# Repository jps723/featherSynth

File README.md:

# Feather Synth Build Notes 9/4/20

A dual-oscillator polyphonic synthesizer project in collaboration with [Bantam Tools](https://www.bantamtools.com/).  The [project build](https://www.hackster.io/news/create-a-synth-and-sequencer-using-bantam-tools-desktop-cnc-milling-machine-83a0fdb942a3) guide is available on Hackster.

**Design Notes:**

The hardware component of this project is centered around the Adafruit Feather M4 Express.  This board has two 12bit DAC pins allowing for stereo audio synthesis, however this project does not use any stereo effects and delivers a mono signal to a 3.5mm mono audio jack.  

The hardware design has 5 inputs in the form of 4 potentiometers and a tactile button.  There are exposed female headers for an Adafruit Feather M4 Express.  The board will only fit in one direction, with the microUSB port facing to the left.  

If you look at the [pinout](https://learn.adafruit.com/adafruit-feather-m4-express-atsamd51/pinouts) of the M4 Express, you’ll see that we are using analog pin A0 as our DAC/audio output, and A2-A5 as our analog inputs.  Our button connects to digital pin 5.

The base software for the device uses these inputs to control an auto-advancing sequence of notes.  The knobs control the root note, the scale (it comes pre-programmed with the 7 diatonic modes), the probability that the note will play, and the time delay between notes/tempo.  Pressing the button will cycle through different waveforms/oscillator types.

**Synthesizer Design**
The synth is a polyphonic dual-oscillator synthesizer, each with independent bi-quad filters and envelopes.  The envelope settings are static while the filters are set to Low Pass Filters with the frequency cutoff randomly changing between two static values based on probability (math within the software -- this is unrelated to the probability knob).   

**Controls**
Root Note (Tonic)
The note from which the scale begins.  By default the notes to choose from range from A0 to C8

**Scale Selector**
There are a total of seven scales to choose from, beginning with the major scale, and then each mode variant resulting in the 7 diatonic modes in western music.

**Probability**
The probability that the note will be played, as calculated by comparing the knob’s position to a randomly generated number. Ex. 0-100% chance of playing

**Tempo**
The overall tempo of the sequence as determined by delay between each note

**Waveform Selector**
This is a series of oscillator combinations that get cycled through using the button.

## **Code**
The code is broken up into two separate files:  

**featherSynth.ino**
This is our primary code and is broken up into two sections: setup and loop.  Setup runs once, while loop cycles through continuously after the setup code has been executed. All of the code above the setup() function is required to call the library we are using (Audio.h), call our reference file (scales.h), and initialize our global variables. All of the code below the main loop() are functions that are called from either within setup() or loop().

Setup() contains code for setting audio memory allocation, pin assignment, and a function called oscillatorSetup() that is used for setting initial values of our oscillators/envelopes, etc.  These will mostly get overwritten by the loop however we want to define our instrument before the program begins to cycle.  

loop() contains the bulk of our code. We have a function called buttonHandler() that is used for managing what we want to happen when we press the button. If you find this function below, you can add further oscillator combinations.  Our potentiometer readings are assigned to the Feather pins here as well. If you want to change the order of the knobs, do it here.

The nested for() loop is used to populate the rootScaled array.  This determines what notes are in the sequence and the order that they’re arranged in.  There are two arrangements to choose from, either climbing the scale, or random selection.  Only one can be used at a time.

The frequency is calculated using a formula that stems from midi note values which are a standard form of notation for relating to frequency.

The frequency cutoff is currently assigned a 50% chance of being 7000 hz, or 2000 hz.  Experiment with these numbers.

The probabilityOfPlaying variable is compared to a random value between 0 and 100.  Since probabilityOfPlaying is also a value between 0 and 100, this is treated as a percentage.  You can experiment with these values.

playOsc1() and playOsc2() functions take one argument (frequency) which is calculated via the explanation above.  These functions also contain the methods for dictating the ADSR envelope values which are hardcoded and can be adjusted and should be experimented with.  The filter frequency cutoff and delayTime are also embedded in these functions, with delayTime being used to set the time between notes (our tempo).

The buttonHandler function counts the button presses and uses that count to cycle through the 7 different oscillator combinations in the switch statement.

scales.h
scales.h is a reference file where we have all of our different scales stored.  The base code has 7 scales (each of the diatonic modes) spread out across two octaves, with the root note at each octave playing at a 3:1 ratio to everything else.  This results in an 18 note array (an array with 18 indices), which are all a part of another array that contains each of these arrays (a total of 7).  If you were to add an 8th scale with 18 notes, then the scales[][] array should be initialized as scales[8][18].  This would also need to be changed in the .ino sketch in the rootScaled[][] array.  

Currently, if the knob is turned all the way to the left, the Ionian (major) Scale is selected.  As the knob is turned to the right, each scale from the array is played in the order that they are presented in the scales.h file.

## Build Process

**TOP**
Bit: 1/64”
Mill Time: ~3mins

**BOTTOM**
Bit: 1/32”, 1/64”
Mill Time: ~11mins

It’s easiest to solder in this order:
```
1. Vias
2. Resistor
3. Headers
4. Audio jack
5. Tactile button
6. Pots
```

Test

First follow [this guide](https://learn.adafruit.com/adafruit-feather-m4-express-atsamd51) for getting acquainted with the board and setting up your arduino IDE to use it. For the SAMD Board Support (Adafruit version), version 1.5.14 is verified to work.  Version 1.6+ has introduced a problem that will break the code without generating any errors.

Additionally, you will need to install the Adafruit fork of the PJRC Audio Library via the IDE.  

And also the following libraries:

```
Adafruit_SPIFlash
Adafruit_Zero_I2S_Library
SDFat-Adafruit Fork
```

Once all of the dependencies have been installed, and you’ve uploaded a trial sketch, upload the code that you’ve downloaded from the repository and have fun!

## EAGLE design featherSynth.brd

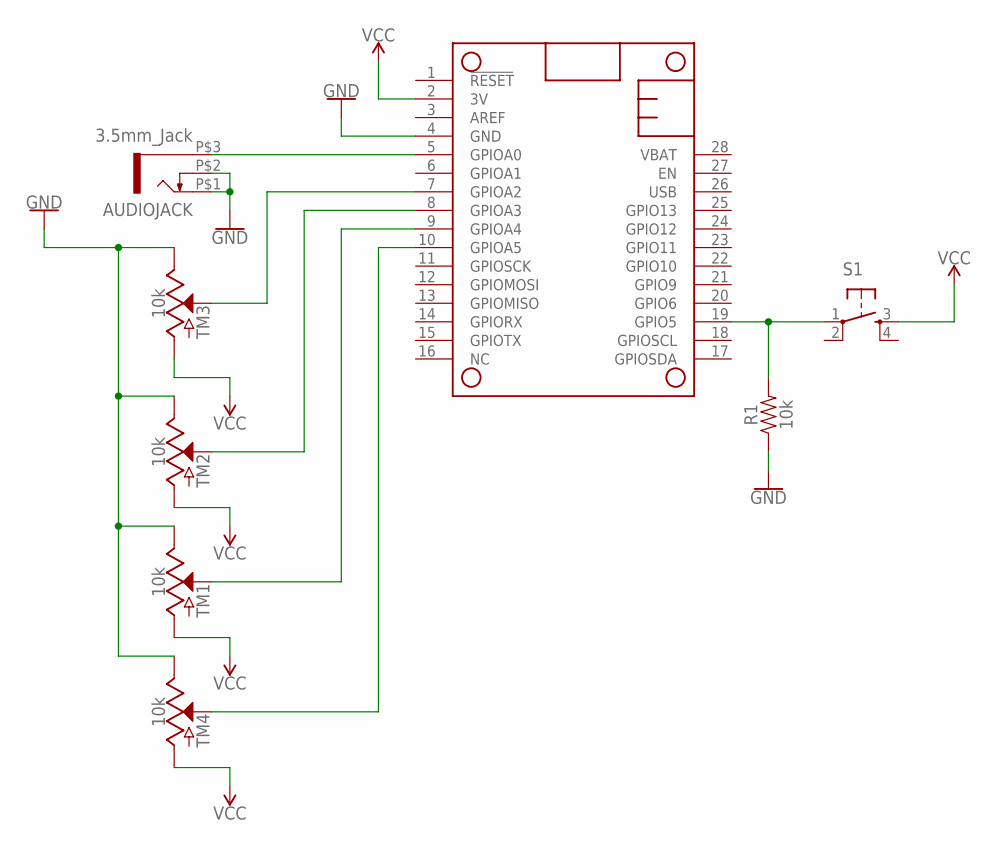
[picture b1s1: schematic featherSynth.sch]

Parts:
AUDIOJACK: 3.5mm_Jack; WQP-PJ301M-12_JACK
MS1: FEATHERWING
R1: 10k; AXIAL-0.3
S1: TAC_SWITCHPTH; TACTILE-PTH
TM1, TM2, TM3, TM4: 10k; POT-PTH-ALPS

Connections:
GND: AUDIOJACK.P$1 (2), AUDIOJACK.P$2 (3), MS1.4 (GND), R1.P$1 (1), TM1.P$1 (E), TM2.P$1 (E), TM3.P$1 (E), TM4.P$1 (E)
unnamed: AUDIOJACK.P$3 (1), MS1.5 (GPIOA0)
unnamed: MS1.8 (GPIOA3), TM2.P$2 (S)
unnamed: MS1.7 (GPIOA2), TM3.P$2 (S)
unnamed: MS1.9 (GPIOA4), TM1.P$2 (S)
unnamed: MS1.10 (GPIOA5), TM4.P$2 (S)
unnamed: MS1.19 (GPIO5), R1.P$2 (2), S1.1
VCC: MS1.2 (3V), S1.3, TM1.P$3 (A), TM2.P$3 (A), TM3.P$3 (A), TM4.P$3 (A)

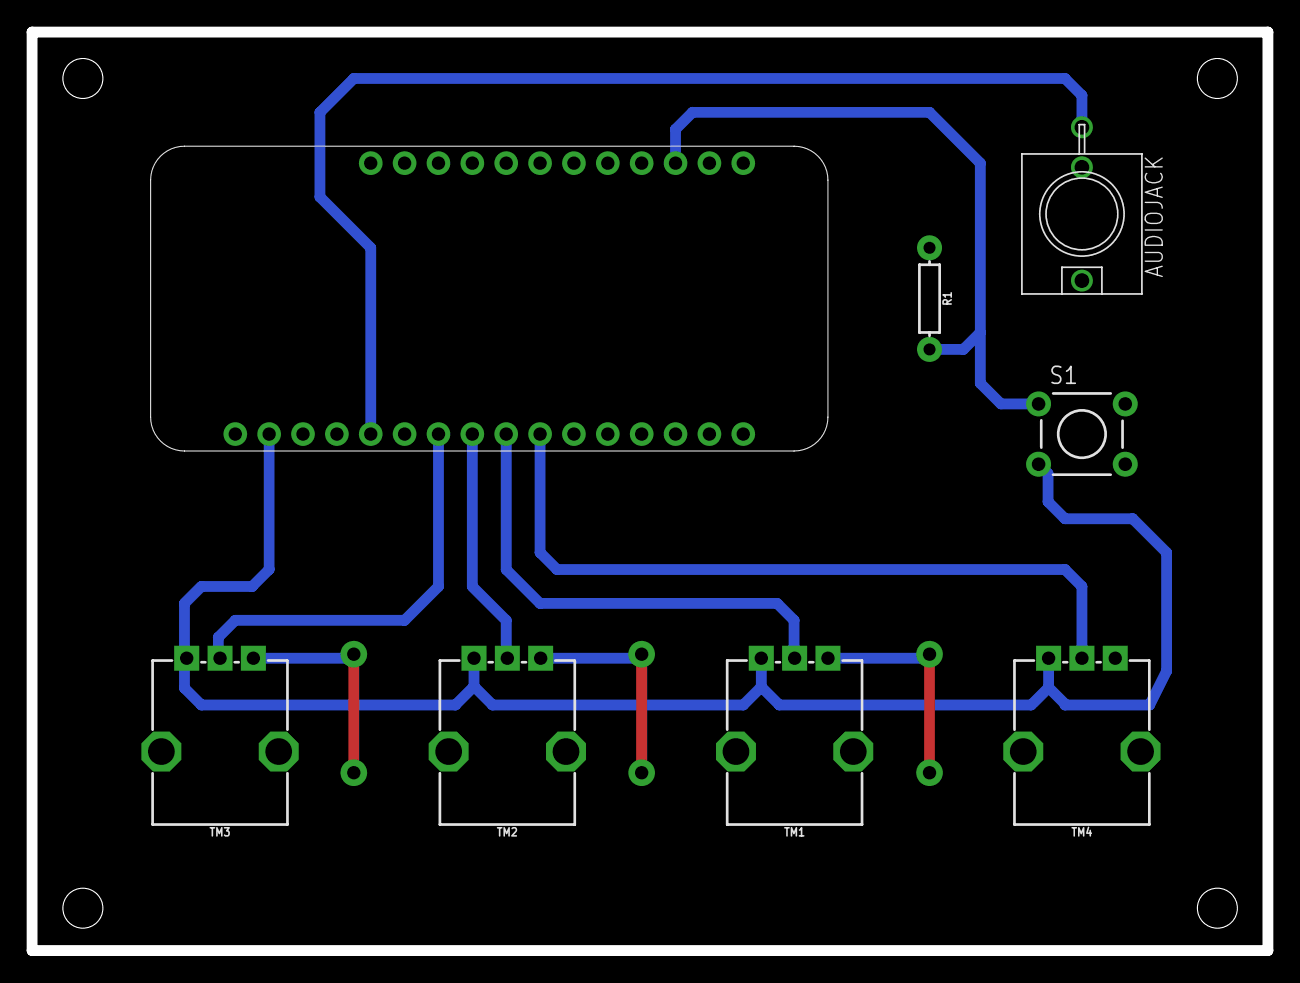
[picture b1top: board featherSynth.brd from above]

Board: 2 copper layers, 92.7 x 68.9 mm, 8 parts (0 on the bottom side), 8 nets.

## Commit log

2020-09-17 Changed global attack settings
2020-09-24 changed knob order
2020-09-24 formatting changes
2020-10-28 added .sch and .brd with updated README
2020-11-02 added images

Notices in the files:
parts and their libraries:
SparkFun-Retired: Licensing: Creative Commons ShareAlike 4.0 International - https://creativecommons.org/licenses/by-sa/4.0
